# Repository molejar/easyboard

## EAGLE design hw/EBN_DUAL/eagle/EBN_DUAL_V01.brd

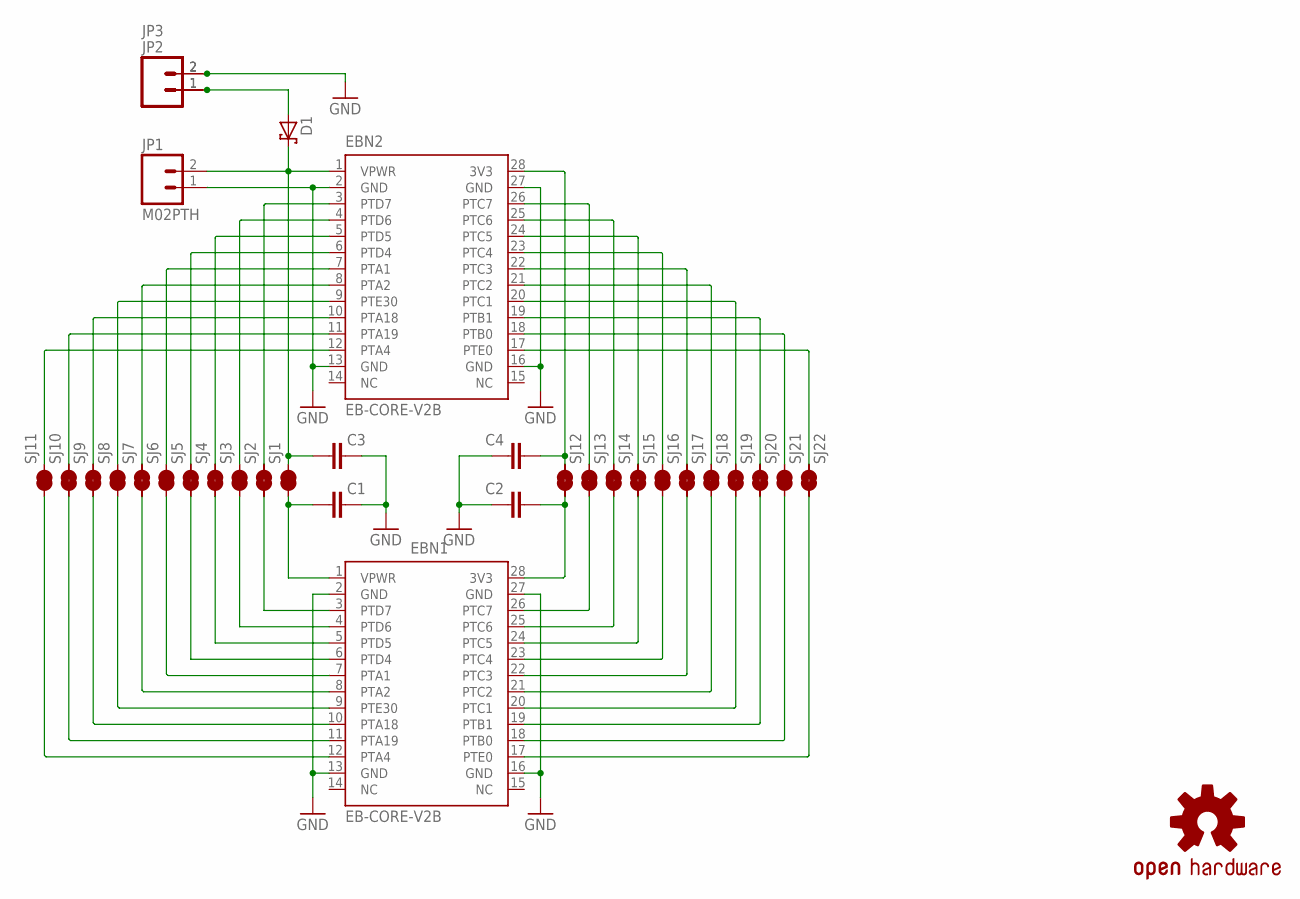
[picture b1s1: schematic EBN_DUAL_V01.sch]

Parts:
C1, C2, C3, C4: C-EUC0603; C0603
D1: PMEG2010BER-SHOTTKY-SOD123FL; SOD-123FL
EBN1, EBN2: EB-CORE-V2B; DIL28-6B
JP1: M02PTH; 1X02
JP2: M02SMD; 1X02-1.25MM_SMD
JP3: M02PTH3; 1X02_LONGPADS
LOGO1: OSHW-LOGOS; OSHW-LOGO-S
SJ1, SJ2, SJ3, SJ4, SJ5, SJ6, SJ7, SJ8, SJ9, SJ10, SJ11, SJ12, SJ13, SJ14, SJ15, SJ16, SJ17, SJ18, SJ19, SJ20, SJ21, SJ22: SJS; JUMPER-SMD-S1XS

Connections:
GND: C1.2, C2.1, C3.2, C4.1, EBN1.2 (GND), EBN1.13 (GND), EBN1.16 (GND), EBN1.27 (GND), EBN2.2 (GND), EBN2.13 (GND), EBN2.16 (GND), EBN2.27 (GND), JP1.1, JP2.2, JP3.2
unnamed: C4.2, EBN2.28 (3V3), SJ12.2
unnamed: EBN1.26 (PTC7), SJ13.1
unnamed: EBN2.26 (PTC7), SJ13.2
unnamed: EBN2.25 (PTC6), SJ14.2
unnamed: EBN2.24 (PTC5), SJ15.2
unnamed: EBN2.23 (PTC4), SJ16.2
unnamed: EBN2.22 (PTC3), SJ17.2
unnamed: EBN2.21 (PTC2), SJ18.2
unnamed: EBN2.20 (PTC1), SJ19.2
unnamed: EBN2.19 (PTB1), SJ20.2
unnamed: EBN2.18 (PTB0), SJ21.2
unnamed: EBN2.17 (PTE0), SJ22.2
unnamed: EBN2.7 (PTA1), SJ6.2
unnamed: C3.1, D1.C, EBN2.1 (VPWR), JP1.2, SJ1.2
unnamed: D1.A, JP2.1, JP3.1
unnamed: EBN2.3 (PTD7), SJ2.2
unnamed: EBN2.4 (PTD6), SJ3.2
unnamed: EBN2.5 (PTD5), SJ4.2
unnamed: EBN2.6 (PTD4), SJ5.2
unnamed: EBN2.8 (PTA2), SJ7.2
unnamed: EBN2.9 (PTE30), SJ8.2
unnamed: EBN2.10 (PTA18), SJ9.2
unnamed: EBN2.11 (PTA19), SJ10.2
unnamed: EBN2.12 (PTA4), SJ11.2
unnamed: C1.1, EBN1.1 (VPWR), SJ1.1
unnamed: EBN1.3 (PTD7), SJ2.1
unnamed: EBN1.4 (PTD6), SJ3.1
unnamed: EBN1.5 (PTD5), SJ4.1
unnamed: EBN1.6 (PTD4), SJ5.1
unnamed: EBN1.7 (PTA1), SJ6.1
unnamed: EBN1.8 (PTA2), SJ7.1
unnamed: EBN1.9 (PTE30), SJ8.1
unnamed: EBN1.10 (PTA18), SJ9.1
unnamed: EBN1.11 (PTA19), SJ10.1
unnamed: EBN1.12 (PTA4), SJ11.1
unnamed: C2.2, EBN1.28 (3V3), SJ12.1
unnamed: EBN1.25 (PTC6), SJ14.1
unnamed: EBN1.24 (PTC5), SJ15.1
unnamed: EBN1.23 (PTC4), SJ16.1
unnamed: EBN1.22 (PTC3), SJ17.1
unnamed: EBN1.21 (PTC2), SJ18.1
unnamed: EBN1.20 (PTC1), SJ19.1
unnamed: EBN1.19 (PTB1), SJ20.1
unnamed: EBN1.18 (PTB0), SJ21.1
unnamed: EBN1.17 (PTE0), SJ22.1

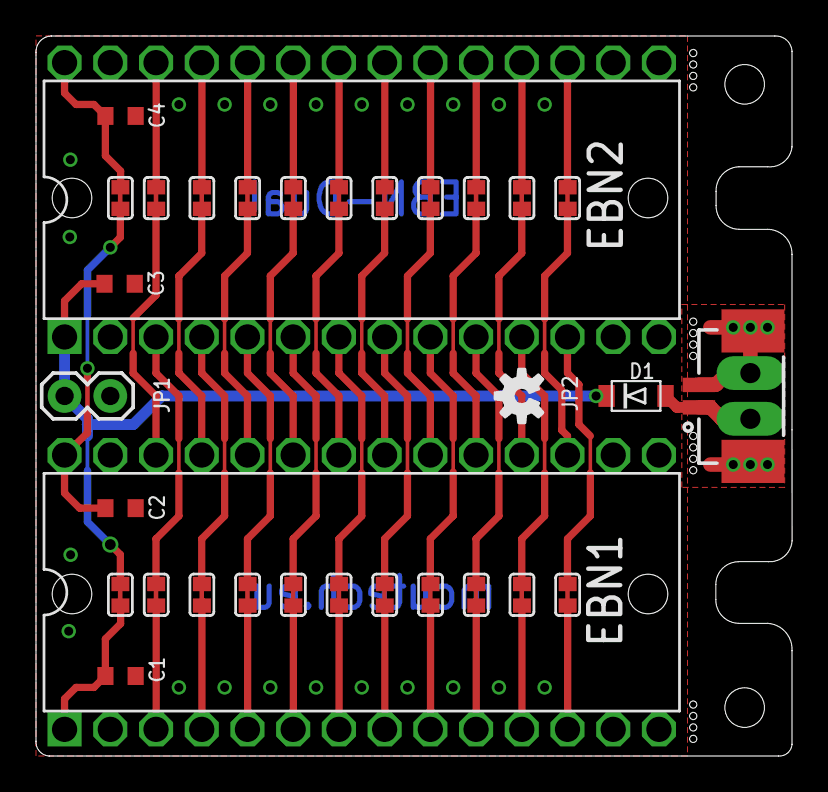
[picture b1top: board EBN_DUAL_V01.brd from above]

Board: 2 copper layers, 42.0 x 40.0 mm, 33 parts (0 on the bottom side), 46 nets.
